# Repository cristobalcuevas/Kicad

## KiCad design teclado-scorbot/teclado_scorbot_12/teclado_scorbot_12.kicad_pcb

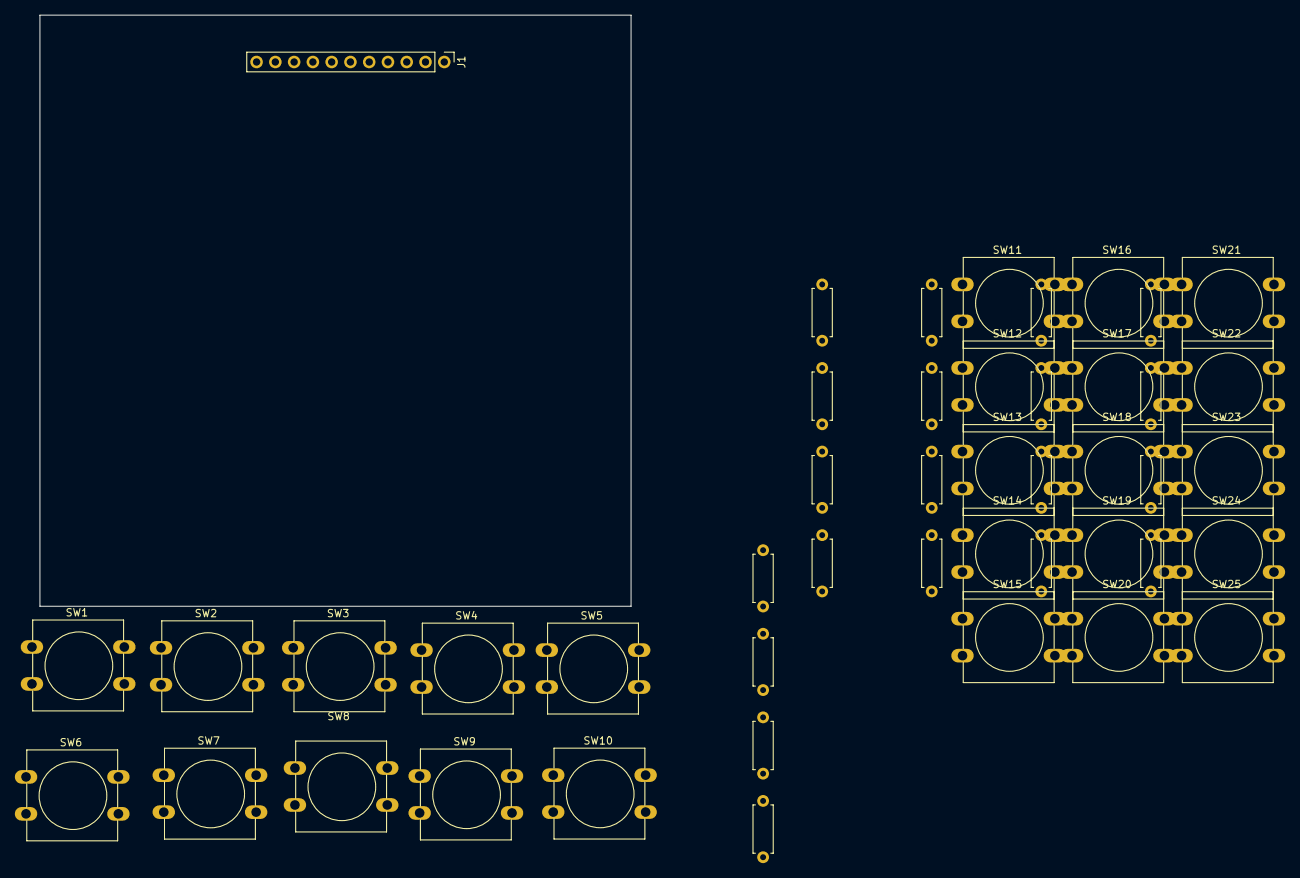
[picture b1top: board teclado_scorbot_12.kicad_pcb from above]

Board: 2 copper layers, 80.0 x 80.0 mm, 46 parts (0 on the bottom side), 30 nets, no tracks yet.

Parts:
J1: Conn_01x11; PinHeader_1x11_P2.54mm_Vertical
R1, R2, R3, R4, R5, R6, R7, R8, R9, R10, R11, R12, R13, R14, R15, R16, R17, R18, R19, R20: 0R; R_Axial_DIN0207_L6.3mm_D2.5mm_P7.62mm_Horizontal
SW1, SW2, SW3, SW4, SW5, SW6, SW7, SW8, SW9, SW10, SW11, SW12, SW13, SW14, SW15, SW16, SW17, SW18, SW19, SW20, SW21, SW22, SW23, SW24, SW25: SW_Push_Dual; SW_PUSH-12mm

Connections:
/Teclado/01: J1.1, R5.1, SW5.1
/Teclado/02: J1.2, R4.1, SW4.1
/Teclado/03: J1.3, SW21.2, SW22.2, SW23.2, SW24.2, SW25.2
/Teclado/04: J1.4, SW16.2, SW17.2, SW18.2, SW19.2, SW20.2
/Teclado/05: J1.5, SW1.2, SW2.2, SW3.2, SW4.2, SW5.2
/Teclado/06: J1.6, SW6.2, SW7.2, SW8.2, SW9.2, SW10.2
/Teclado/07: J1.7, SW11.2, SW12.2, SW13.2, SW14.2, SW15.2
/Teclado/08: J1.8, R3.1, SW3.1
/Teclado/09: J1.9, R2.1, SW2.1
/Teclado/10: J1.10, R1.1, SW1.1
unnamed: R1.2, R6.1, SW6.1
unnamed: R2.2, R7.1, SW7.1
unnamed: R3.2, R8.1, SW8.1
unnamed: R4.2, R9.1, SW9.1
unnamed: R5.2, R10.1, SW10.1
unnamed: R10.2, R15.1, SW15.1
unnamed: R6.2, R11.1, SW11.1
unnamed: R11.2, R16.1, SW16.1
unnamed: R7.2, R12.1, SW12.1
unnamed: R12.2, R17.1, SW17.1
unnamed: R8.2, R13.1, SW13.1
unnamed: R13.2, R18.1, SW18.1
unnamed: R9.2, R14.1, SW14.1
unnamed: R14.2, R19.1, SW19.1
unnamed: R15.2, R20.1, SW20.1
unnamed: R16.2, SW21.1
unnamed: R17.2, SW22.1
unnamed: R18.2, SW23.1
unnamed: R19.2, SW24.1
unnamed: R20.2, SW25.1

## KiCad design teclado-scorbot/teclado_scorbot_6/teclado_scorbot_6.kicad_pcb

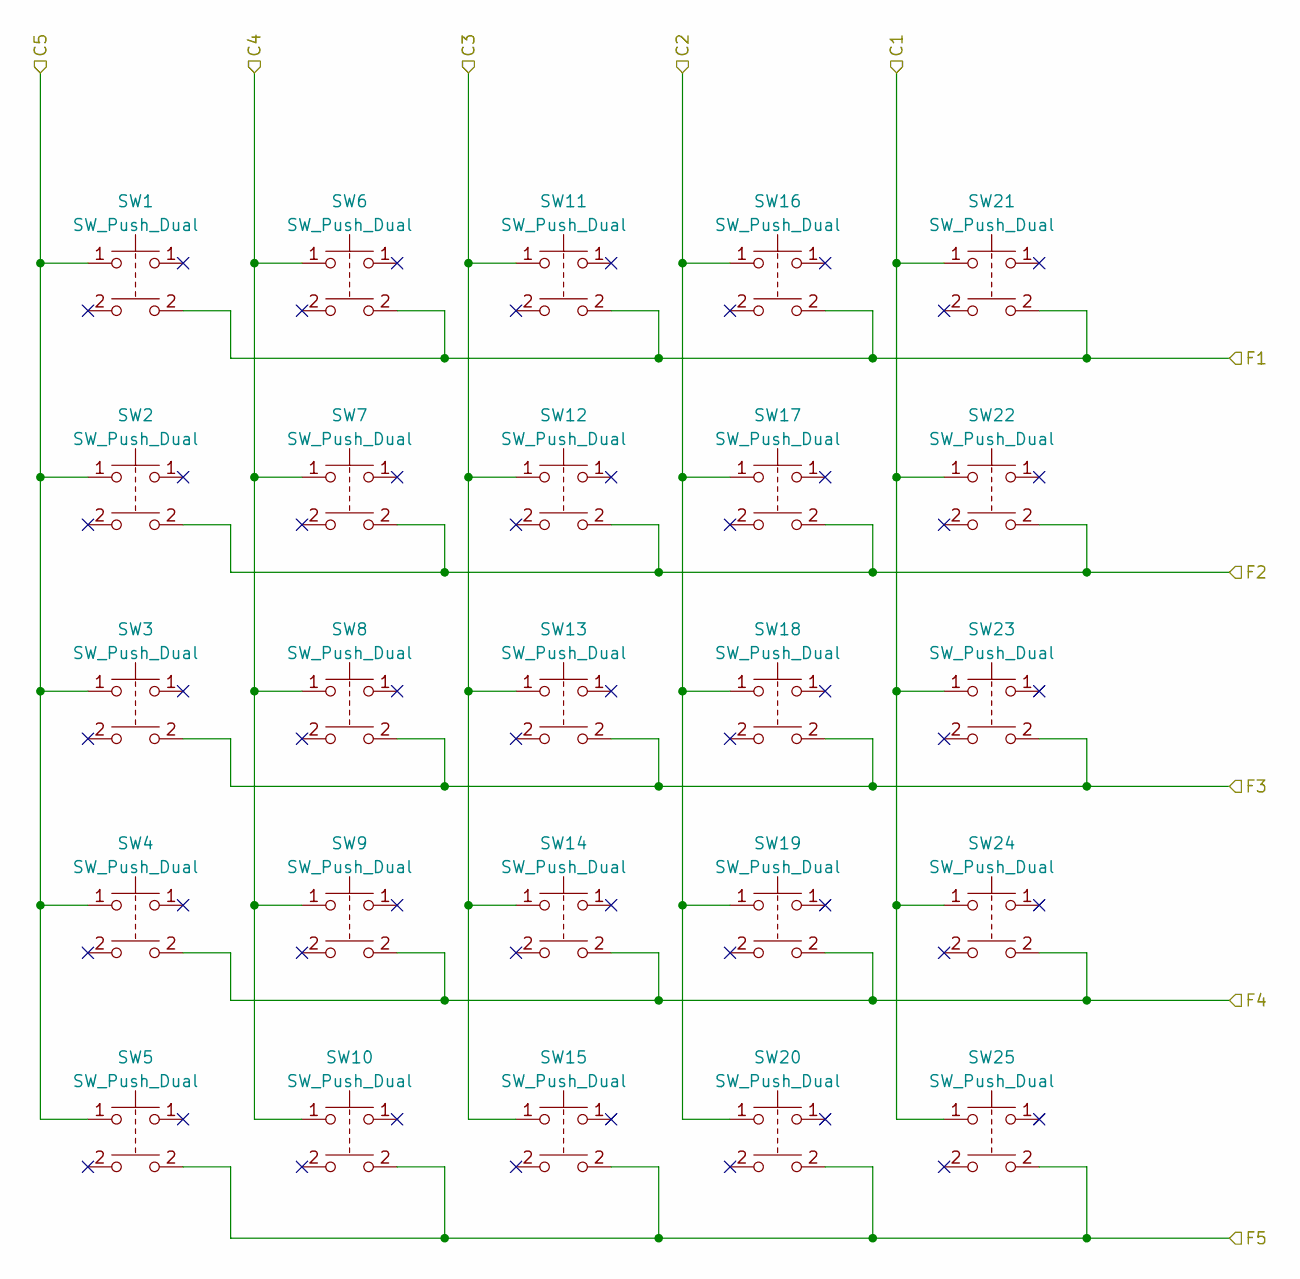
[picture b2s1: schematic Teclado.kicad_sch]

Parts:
SW1, SW2, SW3, SW4, SW5, SW6, SW7, SW8, SW9, SW10, SW11, SW12, SW13, SW14, SW15, SW16, SW17, SW18, SW19, SW20, SW21, SW22, SW23, SW24, SW25: SW_Push_Dual; SW_PUSH_6mm

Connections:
/Teclado/C1: SW21.1, SW22.1, SW23.1, SW24.1, SW25.1; also elsewhere on the board
/Teclado/C2: SW16.1, SW17.1, SW18.1, SW19.1, SW20.1; also elsewhere on the board
/Teclado/C3: SW11.1, SW12.1, SW13.1, SW14.1, SW15.1; also elsewhere on the board
/Teclado/C4: SW6.1, SW7.1, SW8.1, SW9.1, SW10.1; also elsewhere on the board
/Teclado/C5: SW1.1, SW2.1, SW3.1, SW4.1, SW5.1; also elsewhere on the board
/Teclado/F1: SW1.2, SW6.2, SW11.2, SW16.2, SW21.2; also elsewhere on the board
/Teclado/F2: SW2.2, SW7.2, SW12.2, SW17.2, SW22.2; also elsewhere on the board
/Teclado/F3: SW3.2, SW8.2, SW13.2, SW18.2, SW23.2; also elsewhere on the board
/Teclado/F4: SW4.2, SW9.2, SW14.2, SW19.2, SW24.2; also elsewhere on the board
/Teclado/F5: SW5.2, SW10.2, SW15.2, SW20.2, SW25.2; also elsewhere on the board

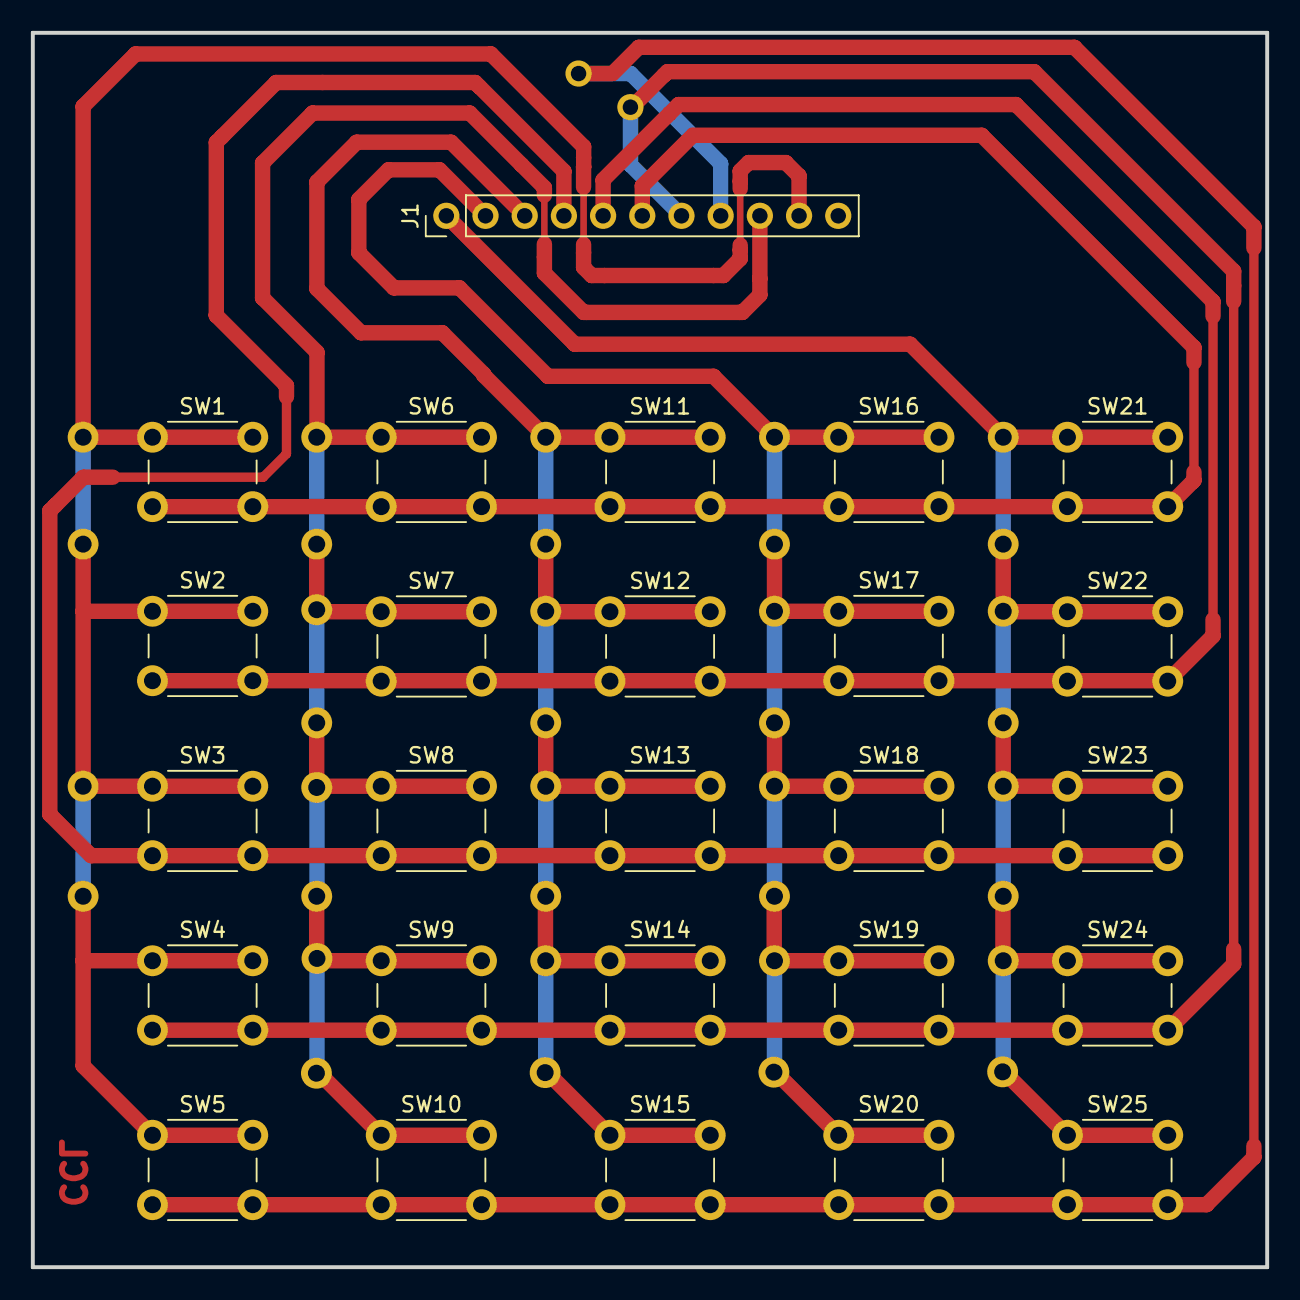
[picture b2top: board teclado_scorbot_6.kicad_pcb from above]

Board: 2 copper layers, 80.0 x 80.0 mm, 26 parts (0 on the bottom side), 10 nets.

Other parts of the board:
J1: Conn_01x11; PinHeader_1x11_P2.54mm_Vertical

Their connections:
/Teclado/C1: J1.1; also elsewhere on the board
/Teclado/C2: J1.2; also elsewhere on the board
/Teclado/C3: J1.3; also elsewhere on the board
/Teclado/C4: J1.9; also elsewhere on the board
/Teclado/C5: J1.10; also elsewhere on the board
/Teclado/F1: J1.6; also elsewhere on the board
/Teclado/F2: J1.5; also elsewhere on the board
/Teclado/F3: J1.4; also elsewhere on the board
/Teclado/F4: J1.7; also elsewhere on the board
/Teclado/F5: J1.8; also elsewhere on the board
